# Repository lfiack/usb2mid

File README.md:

# usb2mid
Small USB to MIDI bridge

## Make the project work
This project uses a submodule for the KiCAD library. To get it properly, use the `--recursive` option when cloning the repo :

```bash
git clone --recursive git@github.com:lfiack/usb2mid.git
```

If you forgot the `--recursive` option (as I do quite often), you can type the following command :

```bash
git submodule update --init --recursive
```

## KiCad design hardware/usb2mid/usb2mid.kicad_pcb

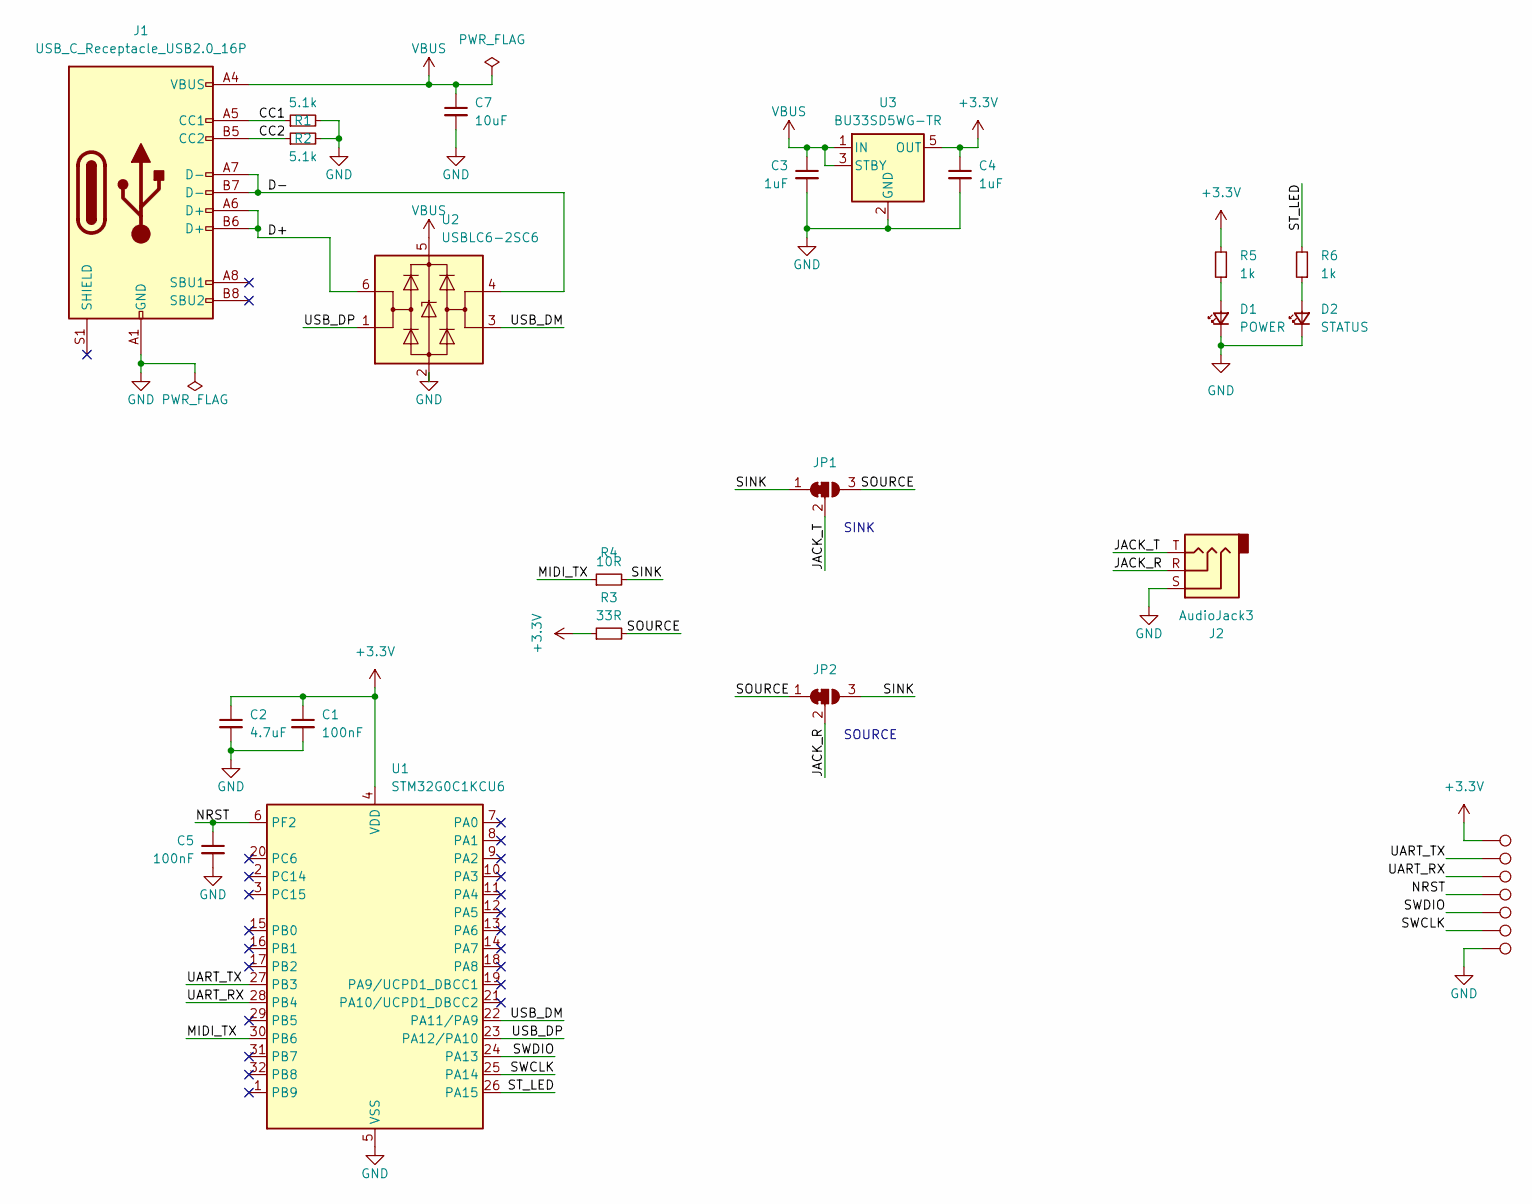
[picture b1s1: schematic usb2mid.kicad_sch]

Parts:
C1, C5: 100nF; C_0402_1005Metric
C2: 4.7uF; C_0603_1608Metric
C3, C4: 1uF; C_0402_1005Metric
C7: 10uF; C_0603_1608Metric
D1: POWER; LED_0603_1608Metric
D2: STATUS; LED_0603_1608Metric
J1: USB_C_Receptacle_USB2.0_16P; USB_C_Receptacle_GCT_USB4105-xx-A_16P_TopMnt_Horizontal
J2: AudioJack3; Jack_3.5mm_CUI_SJ-3523-SMT_Horizontal; Mouser 490-SJ-3523-SMT-TR
JP1, JP2: SolderJumper_3_Bridged12; SolderJumper-3_P1.3mm_Bridged12_RoundedPad1.0x1.5mm
R1, R2: 5.1k; R_0402_1005Metric
R3: 33R; R_0805_2012Metric
R4: 10R; R_0805_2012Metric
R5, R6: 1k; R_0603_1608Metric
TP1, TP2, TP3, TP4, TP5, TP6, TP7: TestPoint; TestPoint_Pad_D1.0mm
U1: STM32G0C1KCU6; QFN-32-1EP_5x5mm_P0.5mm_EP3.45x3.45mm; Mouser 511-STM32G0C1KCU6
U2: USBLC6-2SC6; SOT-23-6
U3: BU33SD5WG-TR; SOT-23-5

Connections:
+3.3V: C1.1, C2.1, C4.1, R3.1, R5.2, TP7.1, U1.4 (VDD), U3.5 (OUT)
/CC1: J1.A5 (CC1), R1.1
/CC2: J1.B5 (CC2), R2.1
/D+: J1.A6 (D+), J1.B6 (D+), U2.6 (I/O1)
/D-: J1.A7 (D-), J1.B7 (D-), U2.4 (I/O2)
/JACK_R: J2.R, JP2.2 (C)
/JACK_T: J2.T, JP1.2 (C)
/MIDI_TX: R4.1, U1.30 (PB6)
/NRST: C5.1, TP3.1, U1.6 (PF2)
/SINK: JP1.1 (A), JP2.3 (B), R4.2
/SOURCE: JP1.3 (B), JP2.1 (A), R3.2
/ST_LED: R6.2, U1.26 (PA15)
/SWCLK: TP5.1, U1.25 (PA14)
/SWDIO: TP4.1, U1.24 (PA13)
/UART_RX: TP2.1, U1.28 (PB4)
/UART_TX: TP1.1, U1.27 (PB3)
/USB_DM: U1.22 (PA11/PA9), U2.3 (I/O2)
/USB_DP: U1.23 (PA12/PA10), U2.1 (I/O1)
GND: C1.2, C2.2, C3.2, C4.2, C5.2, C7.2, D1.1 (K), D2.1 (K), J1.A1 (GND), J1.A12 (GND), J1.B1 (GND), J1.B12 (GND), J2.S, R1.2, R2.2, TP6.1, U1.5 (VSS), U1.33 (VSS), U2.2 (GND), U3.2 (GND)
unnamed: D1.2 (A), R5.1
unnamed: D2.2 (A), R6.1
VBUS: C3.1, C7.1, J1.A4 (VBUS), J1.A9 (VBUS), J1.B4 (VBUS), J1.B9 (VBUS), U2.5 (VBUS), U3.1 (IN), U3.3 (STBY)

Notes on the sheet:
SOURCE
SINK

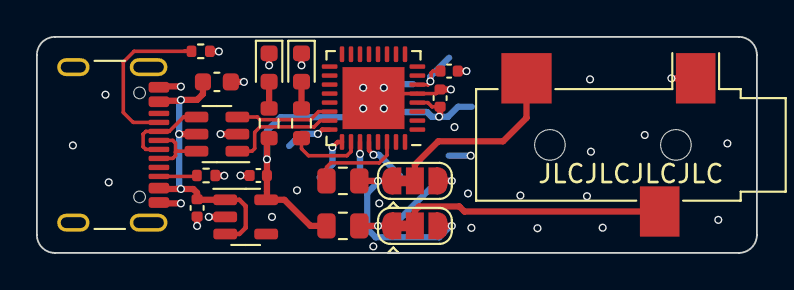
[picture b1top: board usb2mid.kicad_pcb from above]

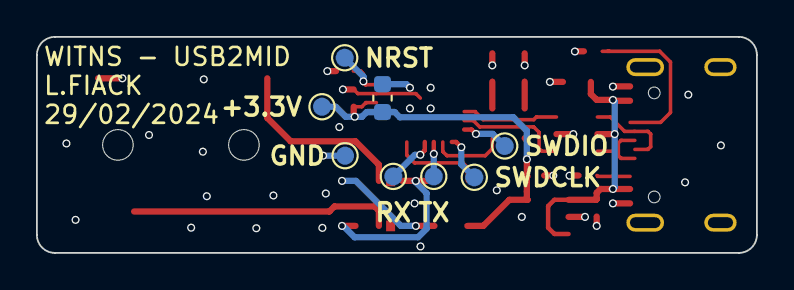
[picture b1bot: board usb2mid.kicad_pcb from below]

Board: 4 copper layers, 40.0 x 12.0 mm, 28 parts (8 on the bottom side), 22 nets.

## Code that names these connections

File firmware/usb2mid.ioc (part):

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Mcu.Name=STM32G0C1K(C-E)Ux
Mcu.Package=UFQFPN32
Mcu.UserName=STM32G0C1KCUx
PA11\ [PA9].Mode=Device
PA11\ [PA9].Signal=USB_DM
PA12\ [PA10].Mode=Device
PA12\ [PA10].Signal=USB_DP
PA13.Mode=Serial_Wire
PA13.Signal=SYS_SWDIO
PA14-BOOT0.Mode=Serial_Wire
PA14-BOOT0.Signal=SYS_SWCLK
PA15.GPIOParameters=GPIO_Label
PA15.GPIO_Label=ST_LED
PA15.Signal=GPIO_Output
PB3.Mode=Asynchronous
PB3.Signal=USART5_TX
PB4.Mode=Asynchronous
PB4.Signal=USART5_RX
PB6.Mode=Asynchronous
PB6.Signal=USART1_TX
PB7.Mode=Asynchronous
PB7.Signal=USART1_RX
RCC.HSE_VALUE=8000000
RCC.SYSCLKFreq_VALUE=64000000
RCC.SYSCLKSource=RCC_SYSCLKSOURCE_PLLCLK
board=custom

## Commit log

2024-02-20 first pcb
2024-02-29 minor corrections + gerber
2024-03-12 changed USB-C footprint
2024-03-28 oops USB ESD!!
2024-03-29 minor corrections to PCB
2024-03-29 solder paste clearance 10%
